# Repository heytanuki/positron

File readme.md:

# Positron

This started as a shitpost, but then it got taken seriously. A maximalist ortholinear dedicated to a beautiful girl. 

### issues

- the split spacebar positioning *sucks* (it's too far to the left)
- the FR4 case needs support in the middle

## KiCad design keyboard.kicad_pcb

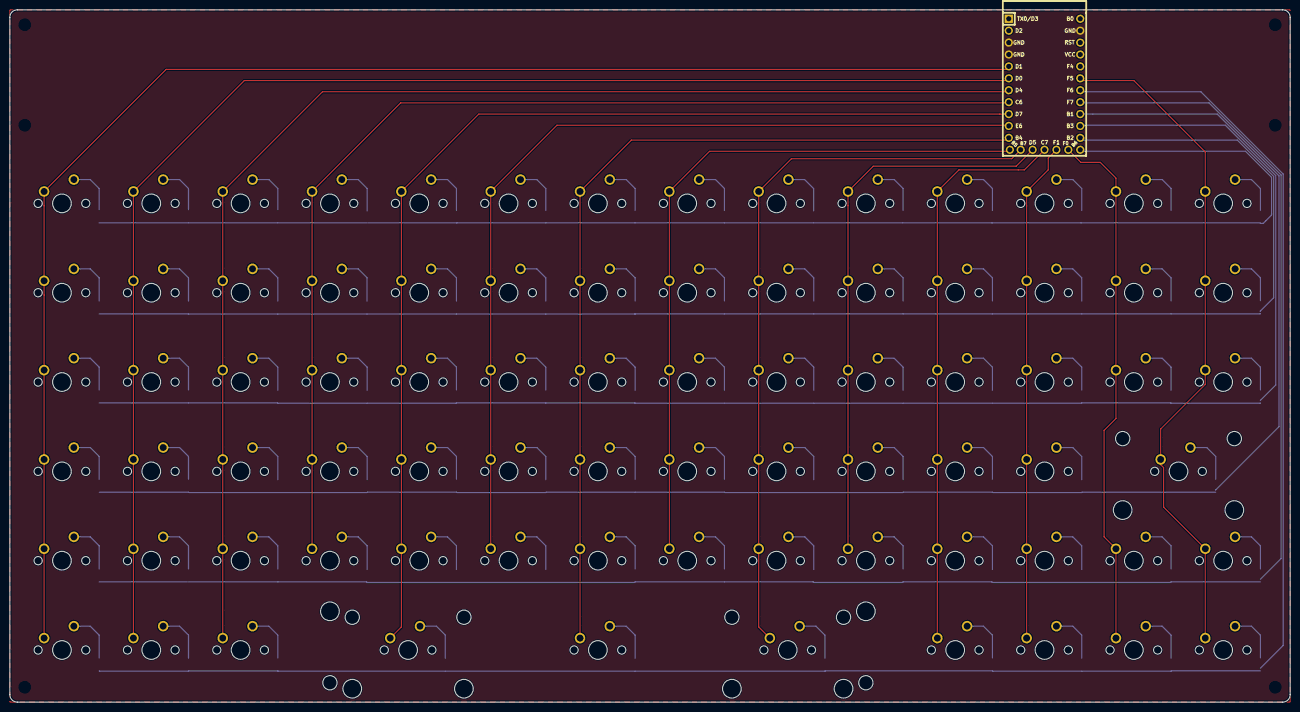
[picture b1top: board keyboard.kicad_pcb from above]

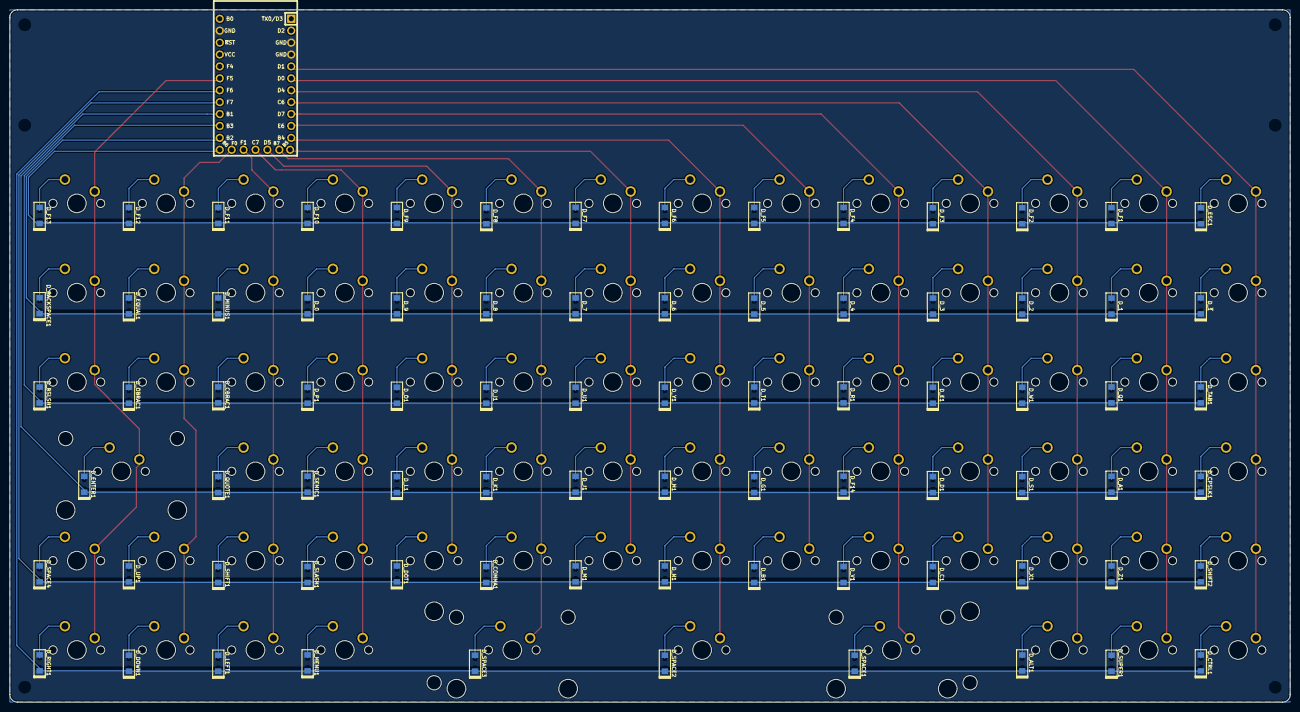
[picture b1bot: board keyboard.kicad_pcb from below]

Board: 2 copper layers, 273.1 x 147.6 mm, 159 parts (79 on the bottom side), 100 nets.

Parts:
D_0, D_1, D_2, D_3, D_4, D_5, D_6, D_7, D_8, D_9: D; D_SOD123
D_A1: D; D_SOD123
D_ALT1: D; D_SOD123
D_B1: D; D_SOD123
D_BACKSPACE1: D; D_SOD123
D_BSLSH1: D; D_SOD123
D_C1: D; D_SOD123
D_CBRAC1: D; D_SOD123
D_COMMA1: D; D_SOD123
D_CPSLK1: D; D_SOD123
D_CTRL1: D; D_SOD123
D_D1: D; D_SOD123
D_DOT1: D; D_SOD123
D_DOWN1: D; D_SOD123
D_E1: D; D_SOD123
D_ENTER1: D; D_SOD123
D_EQUAL1: D; D_SOD123
D_ESC1: D; D_SOD123
D_F1, D_F2, D_F3, D_F4, D_F5, D_F6, D_F7, D_F8, D_F9, D_F10, D_F11, D_F12, D_F13, D_F14: D; D_SOD123
D_G1: D; D_SOD123
D_H1: D; D_SOD123
D_I1: D; D_SOD123
D_J1: D; D_SOD123
D_K1: D; D_SOD123
D_L1: D; D_SOD123
D_LEFT1: D; D_SOD123
D_M1: D; D_SOD123
D_MENU1: D; D_SOD123
D_MINUS1: D; D_SOD123
D_N1: D; D_SOD123
D_O1: D; D_SOD123
D_OBRAC1: D; D_SOD123
D_P1: D; D_SOD123
D_Q1: D; D_SOD123
D_QUOTE1: D; D_SOD123
D_R1: D; D_SOD123
D_RIGHT1: D; D_SOD123
D_S1: D; D_SOD123
D_SEMIC1: D; D_SOD123
D_SHIFT1, D_SHIFT2: D; D_SOD123
D_SLASH1: D; D_SOD123
D_SPACE1, D_SPACE2, D_SPACE3, D_SPACE4: D; D_SOD123
D_SUPER1: D; D_SOD123
D_T1: D; D_SOD123
D_TAB1: D; D_SOD123
D_U1: D; D_SOD123
D_UP1: D; D_SOD123
D_V1: D; D_SOD123
D_W1: D; D_SOD123
D_X1: D; D_SOD123
D_Y1: D; D_SOD123
D_Z1: D; D_SOD123
D_~1: D; D_SOD123
K_0, K_1, K_2, K_3, K_4, K_5, K_6, K_7, K_8, K_9: KEYSW; MXOnly-1U-NoLED
K_A1: KEYSW; MXOnly-1U-NoLED
K_ALT1: KEYSW; MXOnly-1U-NoLED
K_B1: KEYSW; MXOnly-1U-NoLED
K_BACKSPACE1: KEYSW; MXOnly-1U-NoLED
K_BSLSH1: KEYSW; MXOnly-1U-NoLED
K_C1: KEYSW; MXOnly-1U-NoLED
K_CBRAC1: KEYSW; MXOnly-1U-NoLED
K_COMMA1: KEYSW; MXOnly-1U-NoLED
K_CPSLK1: KEYSW; MXOnly-1U-NoLED
K_CTRL1: KEYSW; MXOnly-1U-NoLED
K_D1: KEYSW; MXOnly-1U-NoLED
K_DOT1: KEYSW; MXOnly-1U-NoLED
K_DOWN1: KEYSW; MXOnly-1U-NoLED
K_E1: KEYSW; MXOnly-1U-NoLED
K_ENTER1: KEYSW; MXOnly-2U-NoLED
K_EQUAL1: KEYSW; MXOnly-1U-NoLED
K_ESC1: KEYSW; MXOnly-1U-NoLED
K_F1, K_F2, K_F3, K_F4, K_F5, K_F6, K_F7, K_F8, K_F9, K_F10, K_F11, K_F12, K_F13, K_F14: KEYSW; MXOnly-1U-NoLED
K_G1: KEYSW; MXOnly-1U-NoLED
K_H1: KEYSW; MXOnly-1U-NoLED
K_I1: KEYSW; MXOnly-1U-NoLED
K_J1: KEYSW; MXOnly-1U-NoLED
K_K1: KEYSW; MXOnly-1U-NoLED
K_L1: KEYSW; MXOnly-1U-NoLED
K_LEFT1: KEYSW; MXOnly-1U-NoLED
K_M1: KEYSW; MXOnly-1U-NoLED
K_MENU1: KEYSW; MXOnly-1U-NoLED
K_MINUS1: KEYSW; MXOnly-1U-NoLED
K_N1: KEYSW; MXOnly-1U-NoLED
K_O1: KEYSW; MXOnly-1U-NoLED
K_OBRAC1: KEYSW; MXOnly-1U-NoLED
K_P1: KEYSW; MXOnly-1U-NoLED
K_Q1: KEYSW; MXOnly-1U-NoLED
K_QUOTE1: KEYSW; MXOnly-1U-NoLED
K_R1: KEYSW; MXOnly-1U-NoLED
K_RIGHT1: KEYSW; MXOnly-1U-NoLED
K_S1: KEYSW; MXOnly-1U-NoLED
K_SEMIC1: KEYSW; MXOnly-1U-NoLED
K_SHIFT1, K_SHIFT2: KEYSW; MXOnly-1U-NoLED
K_SLASH1: KEYSW; MXOnly-1U-NoLED
K_SPACE1, K_SPACE3: KEYSW; MXOnly-2.75U-NoLED
K_SPACE2: KEYSW; MXOnly-7U-ReversedStabilizers-NoLED
K_SPACE4: KEYSW; MXOnly-1U-NoLED
K_SUPER1: KEYSW; MXOnly-1U-NoLED
K_T1: KEYSW; MXOnly-1U-NoLED
K_TAB1: KEYSW; MXOnly-1U-NoLED
K_U1: KEYSW; MXOnly-1U-NoLED
K_UP1: KEYSW; MXOnly-1U-NoLED
K_V1: KEYSW; MXOnly-1U-NoLED
K_W1: KEYSW; MXOnly-1U-NoLED
K_X1: KEYSW; MXOnly-1U-NoLED
K_Y1: KEYSW; MXOnly-1U-NoLED
K_Z1: KEYSW; MXOnly-1U-NoLED
K_~1: KEYSW; MXOnly-1U-NoLED
U1: Elite-C

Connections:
GND: U1.3, U1.4, U1.23
unnamed: D_0.2, K_0.2
unnamed: D_1.2, K_1.2
unnamed: D_2.2, K_2.2
unnamed: D_3.2, K_3.2
unnamed: D_4.2, K_4.2
unnamed: D_5.2, K_5.2
unnamed: D_6.2, K_6.2
unnamed: D_7.2, K_7.2
unnamed: D_8.2, K_8.2
unnamed: D_9.2, K_9.2
unnamed: D_A1.2, K_A1.2
unnamed: D_ALT1.2, K_ALT1.2
unnamed: D_B1.2, K_B1.2
unnamed: D_BACKSPACE1.2, K_BACKSPACE1.2
unnamed: D_BSLSH1.2, K_BSLSH1.2
unnamed: D_C1.2, K_C1.2
unnamed: D_CBRAC1.2, K_CBRAC1.2
unnamed: D_COMMA1.2, K_COMMA1.2
unnamed: D_CPSLK1.2, K_CPSLK1.2
unnamed: D_CTRL1.2, K_CTRL1.2
unnamed: D_D1.2, K_D1.2
unnamed: D_DOT1.2, K_DOT1.2
unnamed: D_DOWN1.2, K_DOWN1.2
unnamed: D_E1.2, K_E1.2
unnamed: D_ENTER1.2, K_ENTER1.2
unnamed: D_EQUAL1.2, K_EQUAL1.2
unnamed: D_ESC1.2, K_ESC1.2
unnamed: D_F1.2, K_F1.2
unnamed: D_F2.2, K_F2.2
unnamed: D_F3.2, K_F3.2
unnamed: D_F4.2, K_F4.2
unnamed: D_F5.2, K_F5.2
unnamed: D_F6.2, K_F6.2
unnamed: D_F7.2, K_F7.2
unnamed: D_F8.2, K_F8.2
unnamed: D_F9.2, K_F9.2
unnamed: D_F10.2, K_F10.2
unnamed: D_F11.2, K_F11.2
unnamed: D_F12.2, K_F12.2
unnamed: D_F13.2, K_F13.2
unnamed: D_F14.2, K_F14.2
unnamed: D_G1.2, K_G1.2
unnamed: D_H1.2, K_H1.2
unnamed: D_I1.2, K_I1.2
unnamed: D_J1.2, K_J1.2
unnamed: D_K1.2, K_K1.2
unnamed: D_L1.2, K_L1.2
unnamed: D_LEFT1.2, K_LEFT1.2
unnamed: D_M1.2, K_M1.2
unnamed: D_MENU1.2, K_MENU1.2
unnamed: D_MINUS1.2, K_MINUS1.2
unnamed: D_N1.2, K_N1.2
unnamed: D_O1.2, K_O1.2
unnamed: D_OBRAC1.2, K_OBRAC1.2
unnamed: D_P1.2, K_P1.2
unnamed: D_Q1.2, K_Q1.2
unnamed: D_QUOTE1.2, K_QUOTE1.2
unnamed: D_R1.2, K_R1.2
unnamed: D_RIGHT1.2, K_RIGHT1.2
unnamed: D_S1.2, K_S1.2
unnamed: D_SEMIC1.2, K_SEMIC1.2
unnamed: D_SHIFT1.2, K_SHIFT1.2
unnamed: D_SHIFT2.2, K_SHIFT2.2
unnamed: D_SLASH1.2, K_SLASH1.2
unnamed: D_SPACE1.2, K_SPACE1.2
unnamed: D_SPACE2.2, K_SPACE2.2
unnamed: D_SPACE3.2, K_SPACE3.2
unnamed: D_SPACE4.2, K_SPACE4.2
unnamed: D_SUPER1.2, K_SUPER1.2
unnamed: D_T1.2, K_T1.2
unnamed: D_TAB1.2, K_TAB1.2
unnamed: D_U1.2, K_U1.2
unnamed: D_UP1.2, K_UP1.2
unnamed: D_V1.2, K_V1.2
unnamed: D_W1.2, K_W1.2
unnamed: D_X1.2, K_X1.2
unnamed: D_Y1.2, K_Y1.2
unnamed: D_Z1.2, K_Z1.2
unnamed: D_~1.2, K_~1.2
col0: K_CPSLK1.1, K_CTRL1.1, K_ESC1.1, K_SHIFT2.1, K_TAB1.1, K_~1.1, U1.5
col1: K_1.1, K_A1.1, K_F1.1, K_Q1.1, K_SUPER1.1, K_Z1.1, U1.6
col2: K_2.1, K_ALT1.1, K_F2.1, K_S1.1, K_W1.1, K_X1.1, U1.7
col3: K_3.1, K_C1.1, K_D1.1, K_E1.1, K_F3.1, U1.8
col4: K_4.1, K_F4.1, K_F14.1, K_R1.1, K_SPACE1.1, K_V1.1, U1.9
col5: K_5.1, K_B1.1, K_F5.1, K_G1.1, K_T1.1, U1.10
col6: K_6.1, K_F6.1, K_H1.1, K_N1.1, K_SPACE2.1, K_Y1.1, U1.11
col7: K_7.1, K_F7.1, K_J1.1, K_M1.1, K_U1.1, U1.12
col8: K_8.1, K_COMMA1.1, K_F8.1, K_I1.1, K_K1.1, K_SPACE3.1, U1.25
col9: K_9.1, K_DOT1.1, K_F9.1, K_L1.1, K_O1.1, U1.26
col10: K_0.1, K_F10.1, K_MENU1.1, K_P1.1, K_SEMIC1.1, K_SLASH1.1, U1.27
col11: K_CBRAC1.1, K_F11.1, K_LEFT1.1, K_MINUS1.1, K_QUOTE1.1, K_SHIFT1.1, U1.28
col12: K_DOWN1.1, K_EQUAL1.1, K_F12.1, K_OBRAC1.1, K_UP1.1, U1.29
col13: K_BACKSPACE1.1, K_BSLSH1.1, K_ENTER1.1, K_F13.1, K_RIGHT1.1, K_SPACE4.1, U1.19
row0: D_ESC1.1, D_F1.1, D_F2.1, D_F3.1, D_F4.1, D_F5.1, D_F6.1, D_F7.1, D_F8.1, D_F9.1, D_F10.1, D_F11.1, D_F12.1, D_F13.1, U1.13
row1: D_0.1, D_1.1, D_2.1, D_3.1, D_4.1, D_5.1, D_6.1, D_7.1, D_8.1, D_9.1, D_BACKSPACE1.1, D_EQUAL1.1, D_MINUS1.1, D_~1.1, U1.14
row2: D_BSLSH1.1, D_CBRAC1.1, D_E1.1, D_I1.1, D_O1.1, D_OBRAC1.1, D_P1.1, D_Q1.1, D_R1.1, D_T1.1, D_TAB1.1, D_U1.1, D_W1.1, D_Y1.1, U1.15
row3: D_A1.1, D_CPSLK1.1, D_D1.1, D_ENTER1.1, D_F14.1, D_G1.1, D_H1.1, D_J1.1, D_K1.1, D_L1.1, D_QUOTE1.1, D_S1.1, D_SEMIC1.1, U1.16
row4: D_B1.1, D_C1.1, D_COMMA1.1, D_DOT1.1, D_M1.1, D_N1.1, D_SHIFT1.1, D_SHIFT2.1, D_SLASH1.1, D_SPACE4.1, D_UP1.1, D_V1.1, D_X1.1, D_Z1.1, U1.17
row5: D_ALT1.1, D_CTRL1.1, D_DOWN1.1, D_LEFT1.1, D_MENU1.1, D_RIGHT1.1, D_SPACE1.1, D_SPACE2.1, D_SPACE3.1, D_SUPER1.1, U1.18
